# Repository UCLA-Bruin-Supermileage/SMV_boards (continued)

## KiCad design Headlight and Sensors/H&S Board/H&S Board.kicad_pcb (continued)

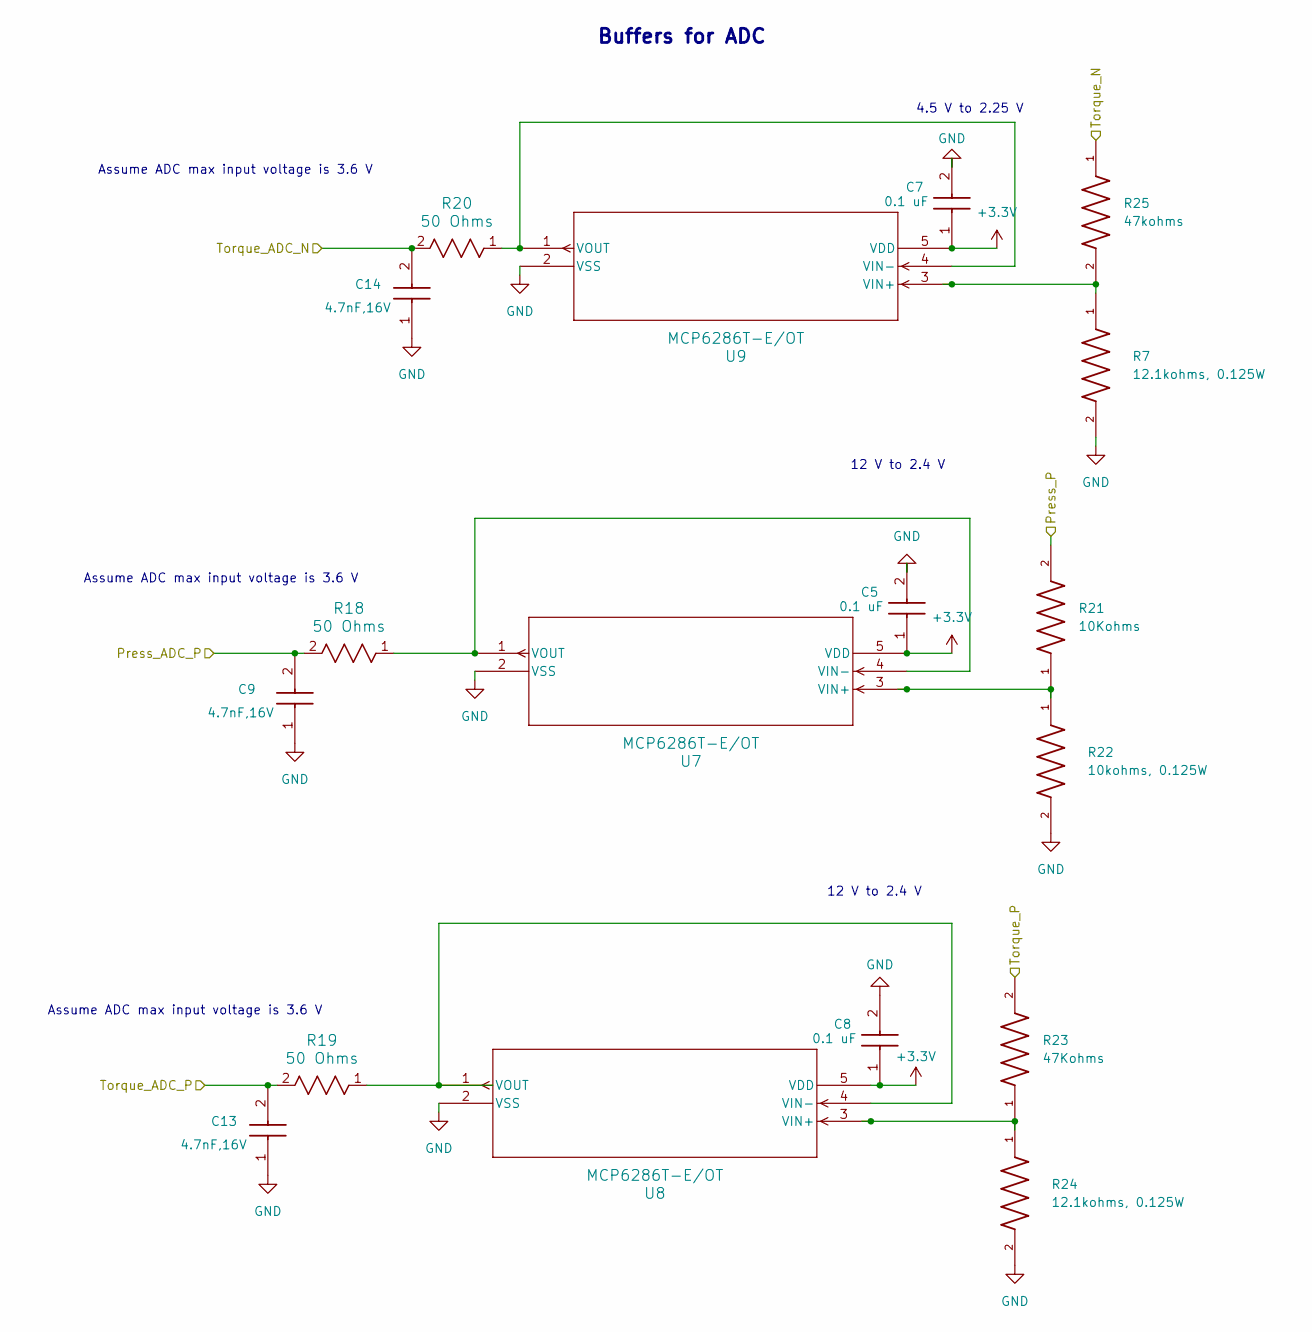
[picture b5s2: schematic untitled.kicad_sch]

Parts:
C5, C7, C8: 0.1 uF; Cap0805; Manufacturer_Part_Number C0805C475K4RACTU; Mouser Part Number 80-C0805C475K4R
C9, C13, C14: 4.7nF,16V; CAPC17595_87N_KEM; Manufacturer_Part_Number C0805C475K4RACTU; Mouser Part Number 80-C0805C475K4R
R7, R24: 12.1kohms, 0.125W; 0603_resistors
R18, R19, R20: 50 Ohms; 0805RESC2012X60N
R21: 10Kohms; RES_TNPW0402_VIS
R22: 10kohms, 0.125W; RES_CRCW_0402
R23: 47Kohms; 0603_resistors
R25: 47kohms; 0603_resistors
U7, U8, U9: MCP6286T-E/OT; SOT-23-5_MC_MCH

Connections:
+3.3V: C5.1, C7.1, C8.1, U7.5 (VDD), U8.5 (VDD), U9.5 (VDD); also elsewhere on the board
/Press_ADC_P: C9.2, R18.2; also elsewhere on the board
/Press_P: R21.2; also elsewhere on the board
/Torque_ADC_N: C14.2, R20.2; also elsewhere on the board
/Torque_ADC_P: C13.2, R19.2; also elsewhere on the board
/Torque_N: R25.1; also elsewhere on the board
/Torque_P: R23.2; also elsewhere on the board
GND: C5.2, C7.2, C8.2, C9.1, C13.1, C14.1, R7.2, R22.2, R24.2, U7.2 (VSS), U8.2 (VSS), U9.2 (VSS); also elsewhere on the board
unnamed: R21.1, R22.1, U7.3 (VIN+)
unnamed: R18.1, U7.1 (VOUT), U7.4 (VIN-)
unnamed: R23.1, R24.1, U8.3 (VIN+)
unnamed: R19.1, U8.1 (VOUT), U8.4 (VIN-)
unnamed: R7.1, R25.2, U9.3 (VIN+)
unnamed: R20.1, U9.1 (VOUT), U9.4 (VIN-)

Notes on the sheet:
12 V to 2.4 V
Assume ADC max input voltage is 3.6 V
Buffers for ADC
12 V to 2.4 V
4.5 V to 2.25 V

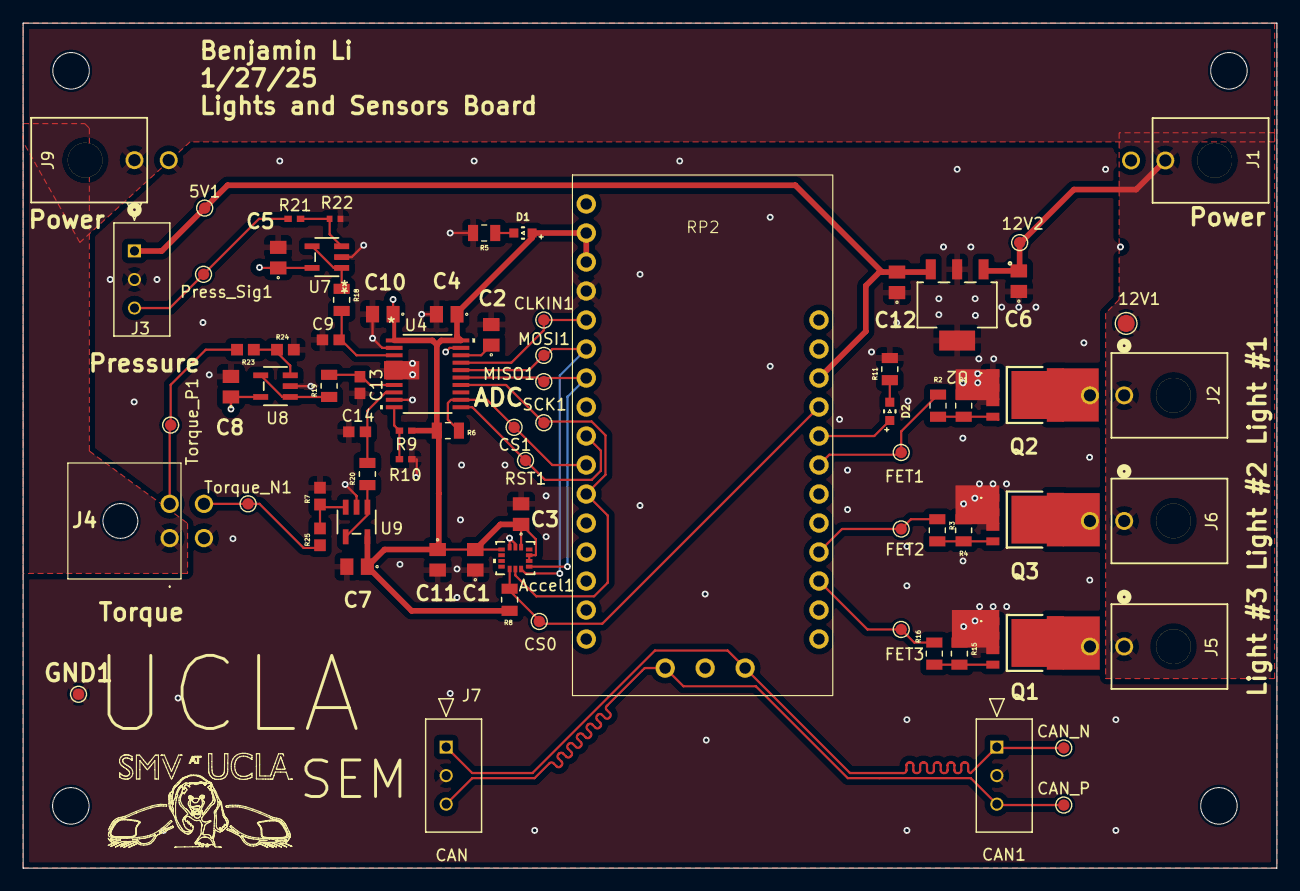
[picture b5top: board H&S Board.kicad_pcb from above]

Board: 2 copper layers, 109.8 x 74.0 mm, 80 parts (0 on the bottom side), 39 nets.

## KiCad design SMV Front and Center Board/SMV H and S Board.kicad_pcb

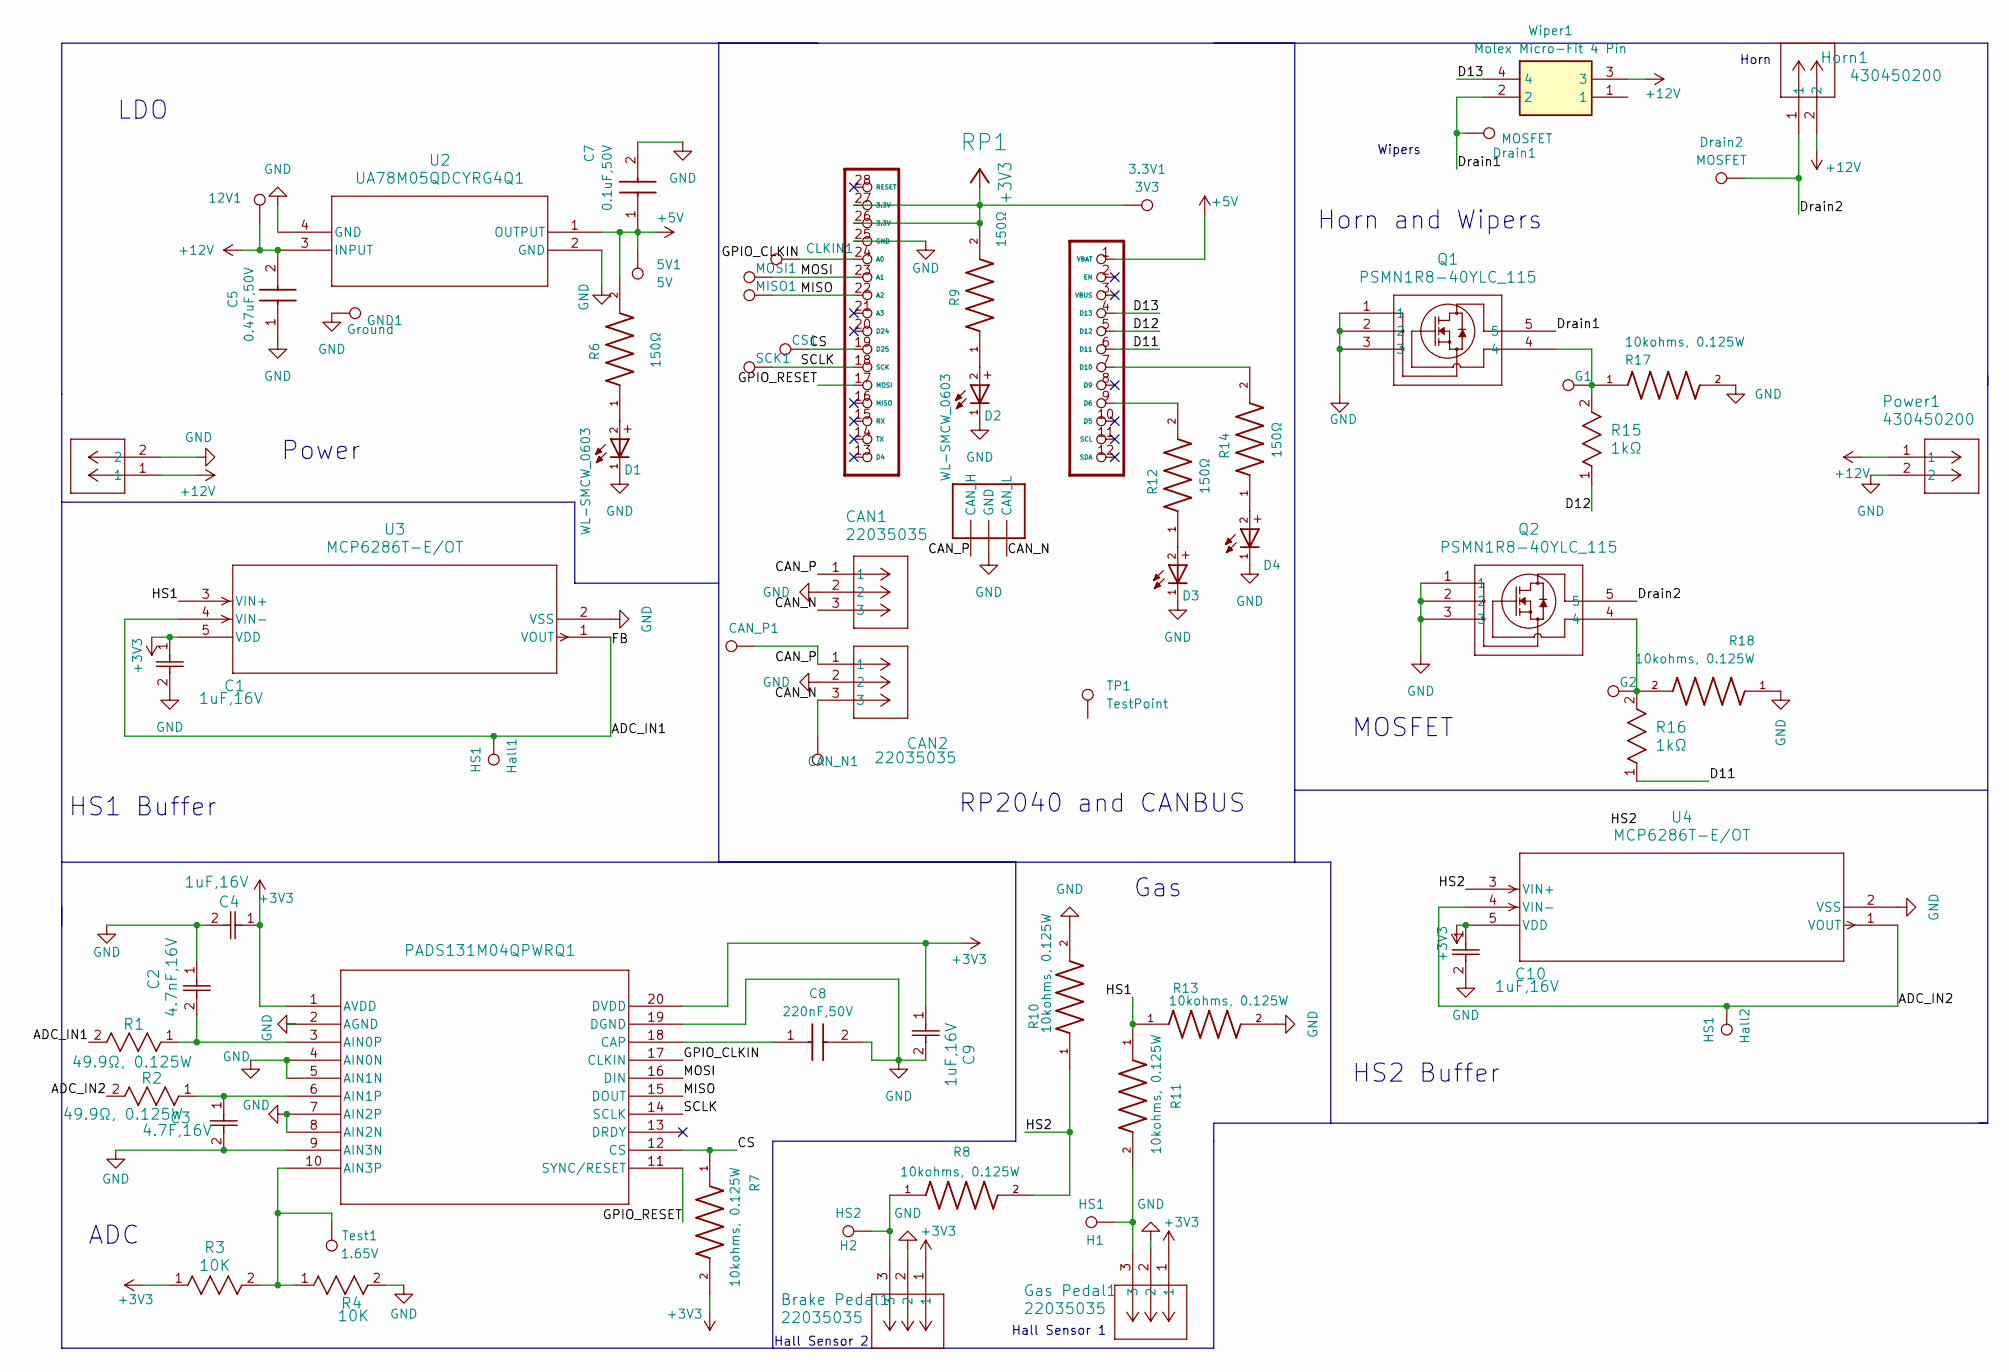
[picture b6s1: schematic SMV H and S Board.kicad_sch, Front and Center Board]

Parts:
3.3V1: 3V3; TestPoint_Pad_D3.0mm
5V1: 5V; TestPoint_Pad_D1.5mm
12V1: 12V; TestPoint_Pad_D3.0mm
Brake Pedal1: 22035035; 3pin_CON_22035035_MOL
C1, C4, C9, C10: 1uF,16V; Cap0805
C2: 4.7nF,16V; CAPC17595_87N_KEM
C3: 4.7F,16V; CAPC17595_87N_KEM
C5: 0.47uF,50V; Cap0805; Manufacturer_Part_Number C0805C334K5RACTU; Mouser Part Number 80-C0805C334K5R
C7: 0.1uF,50V; Cap0805; Manufacturer_Part_Number C0805C104K5RACTU; Mouser Part Number 80-C0805C104K5R
C8: 220nF,50V; CAP_8PACTU
CAN1, CAN2: 22035035; 3pin_CON_22035035_MOL
CAN_N1: 3V3A; TestPoint_Pad_D1.5mm
CAN_P1: 3V3A; TestPoint_Pad_D1.5mm
CLKIN1: 3V3A; TestPoint_Pad_D1.5mm
CS1: 3V3A; TestPoint_Pad_D1.5mm
D1, D2, D3, D4: WL-SMCW_0603; WL-SMCW_0603(diode)
Drain1, Drain2: MOSFET; TestPoint_Pad_D1.5mm
G1, G2: 3V3A; TestPoint_Pad_D1.0mm
GND1: Ground; TestPoint_Pad_D3.0mm
Gas Pedal1: 22035035; 3pin_CON_22035035_MOL
H1: HS1; TestPoint_Pad_D1.5mm
H2: HS2; TestPoint_Pad_D1.5mm
Hall1, Hall2: HS1; TestPoint_Pad_D1.5mm
Horn1: 430450200; CONN_SD-43045-001_02_MOL
J1: 430450200; CONN_SD-43045-001_02_MOL
MISO1: 3V3A; TestPoint_Pad_D1.5mm
MOSI1: 3V3A; TestPoint_Pad_D1.5mm
Power1: 430450200; CONN_SD-43045-001_02_MOL
Q1, Q2: PSMN1R8-40YLC_115; LFPAK56_SOT669_NEX
R1, R2: 49.9Ω, 0.125W; 0805RESC2012X60N
R3, R4: 10K; 0805RESC2012X60N
R6, R9, R12, R14: 150Ω; 0805RESC2012X60N
R7, R8, R10, R11, R13, R17, R18: 10kohms, 0.125W; 0805RESC2012X60N
R15, R16: 1kΩ; 0805RESC2012X60N
RP1: RP2040
SCK1: 3V3A; TestPoint_Pad_D1.5mm
TP1: TestPoint; SEM_logo
Test1: 1.65V; TestPoint_Pad_D1.5mm
U1: PADS131M04QPWRQ1; TSSOP20_PW_TEX
U2: UA78M05QDCYRG4Q1; DCY4_TEX
U3, U4: MCP6286T-E/OT; SOT-23-5_MC_MCH
Wiper1: Molex Micro-Fit 4 Pin; 4_pin0430450401; Manufacturer_Part_Number 0430450401

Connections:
+3V3: 3.3V1.1, Brake Pedal1.1, C1.1, C4.1, C9.1, C10.1, Gas Pedal1.1, R3.1, R7.2, R9.2, RP1.26 (3.3V), RP1.27 (3.3V), U1.1 (AVDD), U1.20 (DVDD), U3.5 (VDD), U4.5 (VDD)
+5V: 5V1.1, C7.1, R6.2, RP1.1 (VBAT), U2.1 (OUTPUT)
+12V: 12V1.1, C5.2, Horn1.2, J1.1, Power1.1, U2.3 (INPUT), Wiper1.3
/ADC_IN1: Hall1.1, R1.2, U3.1 (VOUT), U3.4 (VIN-)
/ADC_IN2: Hall2.1, R2.2, U4.1 (VOUT), U4.4 (VIN-)
/CAN_N: CAN1.3, CAN2.3, CAN_N1.1, RP1.29 (CAN_L)
/CAN_P: CAN1.1, CAN2.1, CAN_P1.1, RP1.31 (CAN_H)
/CS: CS1.1, R7.1, RP1.19 (D25), U1.12 (CS)
/D11: R16.1, RP1.6 (D11)
/D12: R15.1, RP1.5 (D12)
/D13: RP1.4 (D13), Wiper1.4
/Drain1: Drain1.1, Q1.5, Wiper1.2
/Drain2: Drain2.1, Horn1.1, Q2.5
/GPIO_CLKIN: CLKIN1.1, RP1.24 (A0), U1.17 (CLKIN)
/GPIO_RESET: RP1.17 (MOSI), U1.11 (SYNC/RESET)
/HS1: R11.1, R13.1, U3.3 (VIN+)
/HS2: R8.2, R10.1, U4.3 (VIN+)
/MISO: MISO1.1, RP1.22 (A2), U1.15 (DOUT)
/MOSI: MOSI1.1, RP1.23 (A1), U1.16 (DIN)
/SCLK: RP1.18 (SCK), SCK1.1, U1.14 (SCLK)
GND: Brake Pedal1.2, C1.2, C2.1, C3.2, C4.2, C5.1, C7.2, C8.2, C9.2, C10.2, CAN1.2, CAN2.2, D1.1, D2.1, D3.1, D4.1, GND1.1, Gas Pedal1.2, J1.2, Power1.2, Q1.1, Q1.2, Q1.3, Q2.1, Q2.2, Q2.3, R4.2, R10.2, R13.2, R17.2, R18.1, RP1.25 (GND), RP1.30 (GND), U1.2 (AGND), U1.4 (AIN0N), U1.5 (AIN1N), U1.7 (AIN2P), U1.8 (AIN2N), U1.9 (AIN3N), U1.19 (DGND), U2.2 (GND), U2.4 (GND), U3.2 (VSS), U4.2 (VSS)
unnamed: Brake Pedal1.3, H2.1, R8.1
unnamed: D1.2, R6.1
unnamed: D2.2, R9.1
unnamed: D3.2, R12.1
unnamed: D4.2, R14.1
unnamed: G1.1, Q1.4, R15.2, R17.1
unnamed: G2.1, Q2.4, R16.2, R18.2
unnamed: Gas Pedal1.3, H1.1, R11.2
unnamed: R12.2, RP1.9 (D6)
unnamed: R14.2, RP1.7 (D10)
unnamed: C2.2, R1.1, U1.3 (AIN0P)
unnamed: C3.1, R2.1, U1.6 (AIN1P)
unnamed: R3.2, R4.1, Test1.1, U1.10 (AIN3P)
unnamed: C8.1, U1.18 (CAP)

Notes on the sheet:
Hall Sensor 1
Power
Gas
Horn
LDO
RP2040 and CANBUS
MOSFET
Hall Sensor 2
Horn and Wipers
Wipers
HS2 Buffer
HS1 Buffer
ADC

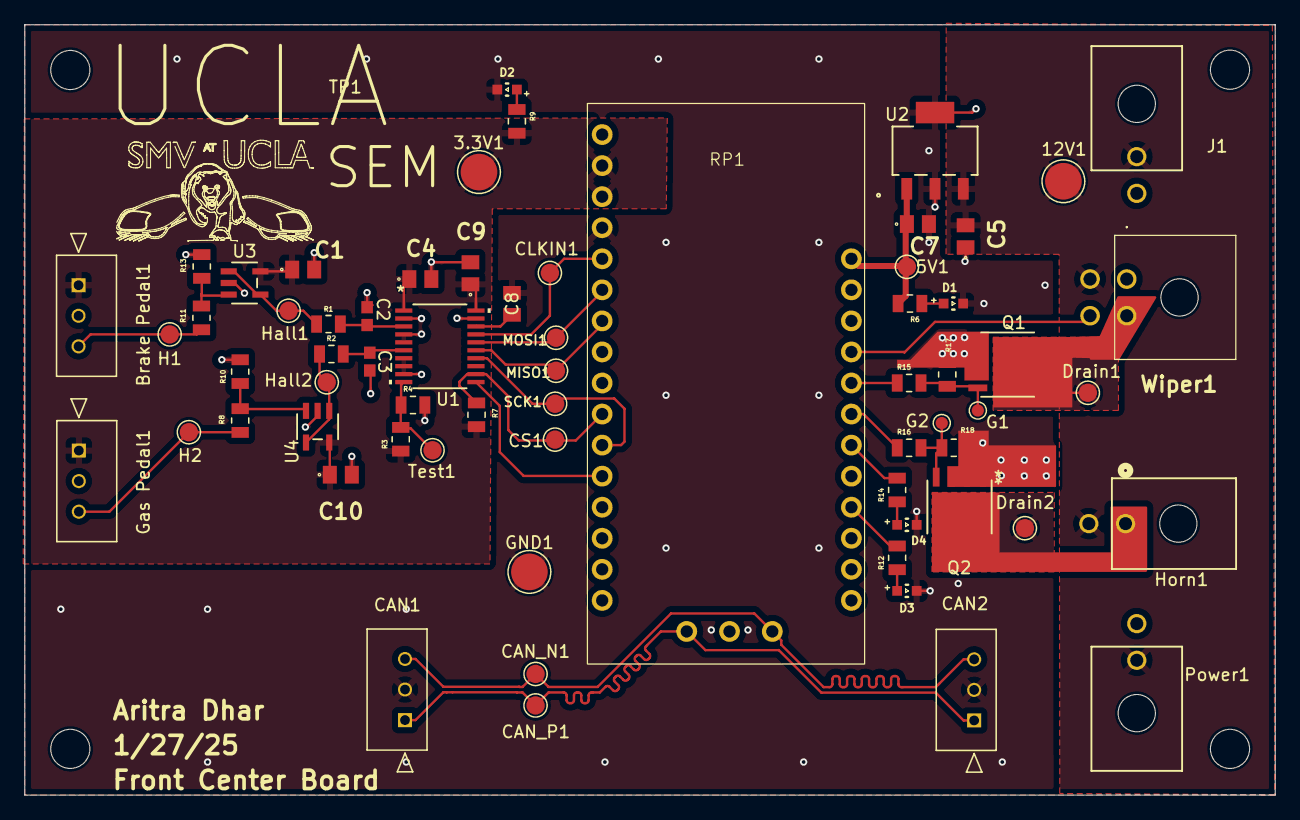
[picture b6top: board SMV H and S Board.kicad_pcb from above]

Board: 2 copper layers, 102.3 x 63.0 mm, 66 parts (0 on the bottom side), 35 nets.

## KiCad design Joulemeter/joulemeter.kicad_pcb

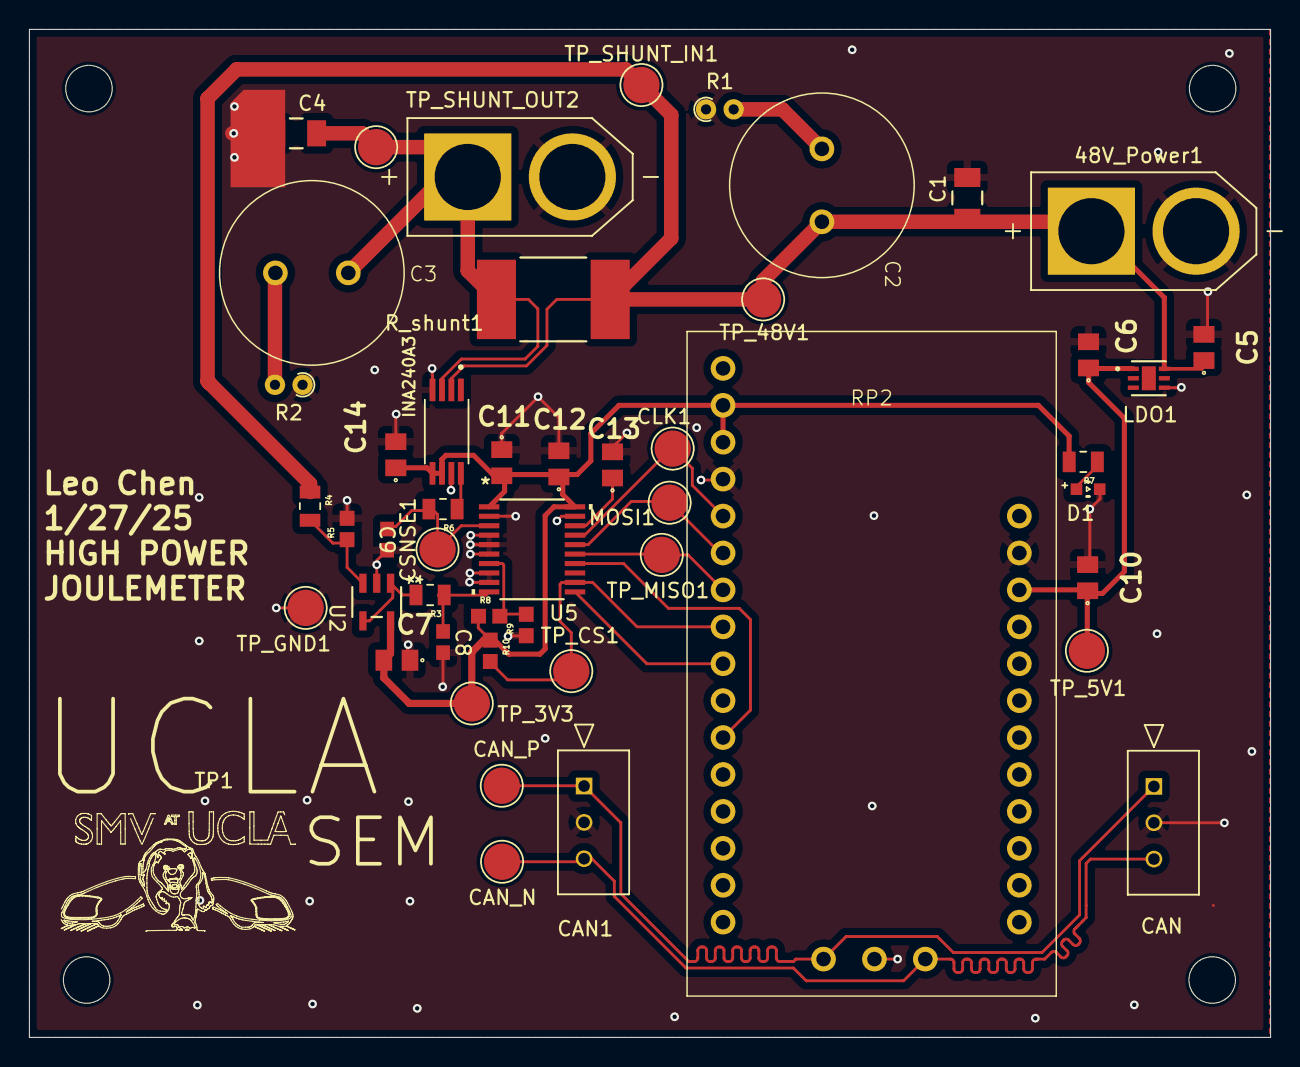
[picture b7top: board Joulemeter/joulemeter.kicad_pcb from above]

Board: 2 copper layers, 85.4 x 69.3 mm, 49 parts (0 on the bottom side), 22 nets.

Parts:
48V_Power1: XT60-M; AMASS_XT60-M
C1, C4: 4.7 µF; CAPC340180_180N_KEM
C2, C3: 470uF, 63V; Big_Chunky_Cap
C5, C11, C12: 1μF; Cap0805
C6: 10μF; Cap0805
C7: 0.1uF; Cap0805
C8, C9: 4.7nF; CAPC17595_87N_KEM
C10: 1 µF; Cap0805
C13: 220nF; Cap0805
C14: 0.1uF,50V; Cap0805
CAN1: 22035035; 3pin_CON_22035035_MOL
CLK1: TestPoint_Pad_D2.5mm
CSNSE1: TestPoint_Pad_D2.5mm
D1: WL-SMCW_0603; WL-SMCW_0603(diode)
INA240A3: SOP65P640X120-8N
J1: XT60-M; AMASS_XT60-M
J3: 22035035; 3pin_CON_22035035_MOL
LDO1: U-DFN2020-6_TYPE-C_DIO-M
MOSI1: TestPoint_Pad_D2.5mm
R1, R2: R_US; R_Axial_DIN0204_L3.6mm_D1.6mm_P1.90mm_Vertical
R3, R6: 50 ohms; 0805RESC2012X60N
R4: 500k ohms; 0805RESC2012X60N
R5, R8, R9, R10: 20k ohms; 0603_resistors
R7: 150 ohm; 0805RESC2012X60N
RP2: RP2040
R_shunt1: 0.0005ohm; RES_PSR400IT_ROM-L
TP1: TestPoint; SEM_logo
TP_3V3, TP_5V1, TP_48V1: TestPoint_Pad_D2.5mm
TP_CS1: TestPoint_Pad_D2.5mm
TP_GND1: TestPoint_Pad_D2.5mm
TP_MISO1: TestPoint_Pad_D2.5mm
TP_SHUNT_IN1: TestPoint_Pad_D2.5mm
TP_SHUNT_OUT2: TestPoint_Pad_D2.5mm
TS_CAN_H1: TestPoint_Pad_D2.5mm
TS_CAN_L2: TestPoint_Pad_D2.5mm
U2: MCP6286T-E/OT; SOT-23-5_MC_MCH
U5: PADS131M04QPWRQ1; TSSOP20_PW_TEX

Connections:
+3V3: C7.2, C11.2, C12.1, C14.1, INA240A3.5 (VS), INA240A3.6 (REF2), R7.2, R8.1, R10.1, RP2.26, RP2.27, TP_3V3.1, U2.5 (VDD), U5.1 (AVDD), U5.20 (DVDD)
+5V: C6.1, C10.1, LDO1.1 (VOUT), RP2.3, TP_5V1.1
+48V: C1.1, C5.1, J1.P (POS), LDO1.6 (VIN), R4.1, R_shunt1.4, TP_48V1.1, TP_SHUNT_IN1.1
/AMP_OUT: R3.2, U2.1 (VOUT), U2.4 (VIN-)
/CAN_H: CAN1.1, J3.1, RP2.1, TS_CAN_H1.1
/CAN_L: CAN1.3, J3.3, TS_CAN_L2.1
/CS: R10.2, RP2.21, TP_CS1.1, U5.12 (CS)
/CSENSE_OUT: C9.1, CSNSE1.1, R6.2, U5.3 (AIN0P)
/GPIO_CLKIN: CLK1.1, RP2.24, U5.17 (CLKIN)
/MISO: RP2.22, TP_MISO1.1, U5.15 (DOUT)
/MOSI: MOSI1.1, RP2.23, U5.16 (DIN)
/RESET: RP2.20, U5.11 (SYNC/RESET)
/SCK: RP2.18, U5.14 (SCLK)
/SHUNT_LOAD: INA240A3.3 (IN-), R_shunt1.2
/Vdivider: C8.1, R3.1, U5.10 (AIN3P)
GND: 48V_Power1.N (NEG), C1.2, C4.2, C5.2, C6.2, C7.1, C8.2, C9.2, C10.2, C11.1, C12.2, C13.2, C14.2, CAN1.2, D1.1, INA240A3.4 (GND), INA240A3.7 (REF1), J1.N (NEG), J3.2, LDO1.4 (GND), R1.1, R2.1, R5.2, R9.1, RP2.2, RP2.25, TP_GND1.1, U2.2 (VSS), U5.2 (AGND), U5.4 (AIN0N), U5.5 (AIN1N), U5.6 (AIN1P), U5.8 (AIN2N), U5.9 (AIN3N), U5.19 (DGND)
unnamed: 48V_Power1.P (POS), C4.1, TP_SHUNT_OUT2.1
unnamed: D1.2, R7.1
unnamed: INA240A3.8 (OUT), R6.1
unnamed: R4.2, R5.1, U2.3 (VIN+)
unnamed: R8.2, R9.2, U5.7 (AIN2P)
unnamed: C13.1, U5.18 (CAP)

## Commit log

2024-12-09 Test branch and project
2024-12-09 Added directories
2024-12-16 adding new project
2024-12-17 added joulemeter project
2024-12-18 progress so far on schematic
2024-12-18 edwin's schematic
2024-12-18 idfk
2024-12-18 ialsodfk
2024-12-18 lmao i suck
2024-12-18 more progress so far on schematic
2024-12-18 rought draft #1
2024-12-18 Added Front and Center Board Project
2024-12-18 Reorganied RPS2040 and ADC
2024-12-19 rough draft of schematic done
2024-12-19 added my joulemeter schematic
2024-12-19 added more connections to things
2024-12-19 fiana's schematic for joulemeter board
2024-12-19 Added necessary grounds and rearranged components. Traces have been limited to node labels for now.
2024-12-21 added some values
2024-12-21 revised version
2024-12-21 revised 12/21
2024-12-21 UI Board added
2024-12-22 not much
2024-12-23 Replaced dummy components, added resistors and capactors, replaced Hall Sensor connectors, replaced wiper connector, reorganized components, added visual divisions
2024-12-23 Fixed issue with resistor
2024-12-23 finished UI Board Schematic
2024-12-23 added test points
2024-12-24 applied suggested changes
2024-12-24 looked at it
2024-12-24 schematic feedback
2024-12-24 new schematic feedback
2024-12-25 edwin's revised schematic 12/24
2024-12-29 UIBoardyay
2024-12-31 edwin's schematic revised 12/30
2024-12-31 extra new fixes
2024-12-31 i forgot to save before pushing
2024-12-31 fixed avdd agnd dvdd dgnd connections
2024-12-31 Implemented new feedback
2025-01-04 edits round 2
2025-01-05 edit #3
2025-01-05 Added 7.2V LDO for wipers
2025-01-06 updated 1/5/25
2025-01-06 some revisions to board
2025-01-06 bypass cap for rp2040
2025-01-06 replaced ina240 with custom symbol
2025-01-07 Fixed readability, added no-connect flags, reoriented grounds
2025-01-07 replaced dummy resistors and caps
2025-01-08 updates to pcb/schematic for 1/7/2025
2025-01-08 my board after grinding some more
2025-01-08 added buffer sheet
2025-01-09 fixed resistance values
2025-01-09 Implemented final checks
2025-01-11 finalized values
2025-01-12 PCB First Layout
2025-01-13 updated 1/12/25
2025-01-14 updated 1/14/25
2025-01-15 updated 1/15/25
2025-01-15 updated second time 1/15/25
2025-01-17 updated 1/16/2025
2025-01-18 PCB Layout Draft and Small Schematic Changes
2025-01-18 Formed compact subsystems
2025-01-18 Compacted wiper and horn connectors
2025-01-19 completed schematic except test points and leds
2025-01-19 finalizing schematic
2025-01-20 RAHHHHH FINISHED MY SCHEMATIC
2025-01-21 Added buffer and reorganized components
2025-01-21 pcb 1/20/25
2025-01-21 updated 1/21/2025
2025-01-22 pcb updated 1/22/25
2025-01-23 updated 1/22/25 again
2025-01-23 Initial commit + schematic draft
2025-01-23 pcb layout progress on jan 22
2025-01-23 third update 1/22/25
2025-01-23 Reorganized
2025-01-23 Organized testpoints and added polygons
2025-01-24 pcb changes 2
2025-01-25 pcb 3
2025-01-25 updated 1/24/25
2025-01-25 pcb 4
2025-01-25 pcb possibly final
2025-01-25 latest schematic and pcb draft
2025-01-25 Reorganized, added filled zones
2025-01-25 updated 1/25/25
2025-01-25 updated again 1/25/2025
2025-01-25 third update 1/25/25
2025-01-26 PCB rough draft
2025-01-26 LFG BOARD DONE FR
2025-01-26 made some changes
2025-01-26 Added ground connections and finalized CAN
2025-01-26 pcb v1384
2025-01-26 almost final
2025-01-26 basically done
2025-01-26 Finalized layout
2025-01-27 Finished!
2025-01-28 Finishedd!
2025-01-28 Finalized!
2025-01-28 small error lol
2025-01-31 Replaced several componentes
2025-02-01 Further component replacement
2025-02-01 gang
2025-02-01 i toast
2025-02-01 helllo
2025-02-01 darn
2025-02-01 im fried
2025-02-02 flub
2025-02-02 hello
2025-02-02 f me
2025-02-02 imsad
2025-02-02 imtired
2025-02-02 almost...
2025-02-02 fuck
2025-02-19 safety board
2025-02-24 component selection
2025-02-24 formatting
2025-02-27 Port accel and ADC files to github
2025-02-28 schematic updates
2025-02-28 updates to schematic
2025-02-28 schematic changes
2025-03-03 4 hydrogen sensors
2025-03-03 replaced adc files with library files
2025-03-05 schematic
2025-03-06 Enabled clkin; autoconvert ouput to voltage
2025-03-06 gitignore update
2025-03-07 added updated UI Board
2025-03-07 updated 3/6
2025-03-08 i think done
2025-03-09 pcb almost done
2025-03-09 pcb
    git commit -m pcb
2025-03-09 maybe possibly final
2025-03-09 text changes
2025-03-11 ldo fixed
2025-03-14 holla
2025-03-14 fuck me
2025-03-26 Update to example .ino code with correct clock Added extra note - must make sure reset pin is correctly specified.
2025-04-20 replacement for prev sketchy adc.begin() bugfix
2025-05-26 Add .DS_Store to .gitignore
2025-05-26 All finished projects + reorganized
2025-05-26 .DS_Store removed!
2025-05-26 Latest project files
2025-05-26 removed extra folder
2025-05-28 Added UI Board and latest code from CAN_2025 repo
2025-05-30 Removed Gerber files and updated UI Board Code
2025-06-03 Adding LP Joule code
2025-06-04 Added latest Safety Board
